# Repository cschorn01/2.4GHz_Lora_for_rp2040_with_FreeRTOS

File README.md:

# Raspberry Pi Pico LoRa Template

<!-- Emoji Cheat Sheet: https://github.com/ikatyang/emoji-cheat-sheet/blob/master/README.md -->

<!--  -->

<!--  -->

## 

The **2.4GHz_Lora_for_rp2040_with_FreeRTOS** is an open source project based on the [Raspberry Pi Pico](https://www.raspberrypi.com/products/raspberry-pi-pico/), [Lora Radio](https://www.semtech.com/products/wireless-rf/lora-connect/sx1280), and [FreeRTOS](https://www.freertos.org/). It's goal is to give hobbyists and developers a strong starting point for their projects involving Lora. This project uses the [PHY layer](https://lora-developers.semtech.com/documentation/tech-papers-and-guides/lora-and-lorawan) of the LoRa radio, with [LoRaWAN](https://lora-developers.semtech.com/documentation/tech-papers-and-guides/lora-and-lorawan) functionality coming.

## 

This project uses a Raspberry Pi Pico's SPI bus to communicate with a 2.4GHz LoRa radio. With FreeRTOS we can create a new task, or individually addressable superloop, that interacts with the [`vSx1280Task`](https://github.com/cschorn01/2.4GHz_Lora_for_rp2040_with_FreeRTOS/blob/44e7e5acd0a1cb4129e875321e36d574b70024c7/src/main.c#L970C6-L970C6) independently. 

In this project there are three tasks, and main():
1. `vSimpleLEDTask` is to show the structure of a task with *setup* above an infinite loop, and the blinking of the onboard pico LED in the infinite loop.
2. `vUsbIOTask` takes typed input from a serial monitor over usb. An unsigned 8 bit pointer array is used as a dynamic ascii character array for a 'string', which is NULL terminated. The address of the pointer array is then sent to `vSx1280Task` to send over LoRa.
3. `vSx1280Task` receives the address of the pointer array from `vUsbIOTask` through a *Task Notification* and reassigns the address to a task local pointer. This is done because there are functions called which delay `vSx1280Task` and would allow `vUsbIOTask` to overwrite the address passed by *Task Notifications*. Once the data is task local `vSx1280Task` will perform a Tx operation, followed by an Rx operation. Both operations are done by using the `sx1280Setup`, `sx1280Tx`, and `sx1280Rx` functions, also in `main.c`.

## 

- :file_folder: pico_projects
  - :file_folder: [Raspberry Pi Pico C SDK](https://github.com/raspberrypi/pico-sdk)
  - :file_folder: [2.4GHz_Lora_for_rp2040_with_FreeRTOS](https://github.com/cschorn01/2.4GHz_Lora_for_rp2040_with_FreeRTOS/) 
    - :file_folder: [Docs](https://github.com/cschorn01/2.4GHz_Lora_for_rp2040_with_FreeRTOS/tree/main/docs)  
    - :file_folder: [FreeRTOS-Kernel](https://github.com/FreeRTOS/FreeRTOS-Kernel)
    - :file_folder: [src](https://github.com/cschorn01/2.4GHz_Lora_for_rp2040_with_FreeRTOS/tree/main/src)  
      - :page_facing_up: [main.c](https://github.com/cschorn01/2.4GHz_Lora_for_rp2040_with_FreeRTOS/blob/main/src/main.c)
    - :file_folder: [include](https://github.com/cschorn01/2.4GHz_Lora_for_rp2040_with_FreeRTOS/tree/main/include)
      - :page_facing_up: [FreeRTOSConfig.h](https://github.com/cschorn01/2.4GHz_Lora_for_rp2040_with_FreeRTOS/tree/main/include/FreeRTOSConfig.h)
    - :page_facing_up: [CMakeLists.txt](https://github.com/cschorn01/2.4GHz_Lora_for_rp2040_with_FreeRTOS/blob/main/CMakeLists.txt)  
    - :page_facing_up: [pico_sdk_import.cmake](https://github.com/cschorn01/2.4GHz_Lora_for_rp2040_with_FreeRTOS/blob/main/pico_sdk_import.cmake)
    - :page_facing_up: [FreeRTOS_Kernel_import.cmake](https://github.com/cschorn01/2.4GHz_Lora_for_rp2040_with_FreeRTOS/blob/main/FreeRTOS_Kernel_import.cmake)

## 

This project is a template to begin a project with a Raspberry Pi Pico, and Lora Modem, for easily adding sensors, or displays.  Then you can create your own long range wireless [Internet of Things](https://en.wikipedia.org/wiki/Internet_of_things) network.  

When adding sensors, create a new task for handling each one. With a new task handling new hardware there must be communication between tasks, which is where [FreeRTOS Task Notifications](https://www.freertos.org/RTOS-task-notifications.html) come in.

In the new task instantiate an 8 bit pointer to store data for sending over SPI:  

>```c
> uint8_t *dataBuffer = NULL;
> ```  
  
Allocate the appropriate amount of memory, in 8 bit chunks, that is needed to send your data:  
  
> ```c
> dataBuffer = ( uint8_t * ) malloc( 255 * sizeof( uint8_t ) );
> ```  

Assign your data to the newly allocated data buffer. Here, 255 is used because it's the maximum LoRa packet size on the sx1280:  
  
>```c
>*( dataBuffer + 0 ) = 0x48; // 0x48 is ASCII Hexadecimal 'H' 
>*( dataBuffer + 1 ) = 0x49; // 0x49 is ASCII Hexadecimal 'I'
>```

Use the [`xTaskNotify()`](https://www.freertos.org/xTaskNotify.html) function to send a *Task Notification* from your new task to `vSx1280Task`. This is where a LoRa message will be sent:

> ```c
> xTaskNotify(  
>             xSx1280TaskHandle,                  /* TaskHandle_t xTaskToNotify */  
>             ( uint32_t ) dataBuffer,            /* uint32_t ulValue (int)&buffer[0] */  
>             eSetValueWithoutOverwrite );        /* eNotifyAction eAction */  
>            )
> ```

To use the incoming *Tast Notification*, it must be reassigned to a task local pointer. This template uses a struct containing an 8 bit pointer:

```c
struct sx1280MessageStorageTillUse{
  uint8_t *message;
};
struct sx1280MessageStorageTillUse messageStorageTillUse = { NULL };
```

<!-- Forkers

 -->

## 

-  `arm-none-eabi-gcc: fatal error: cannot read spec file 'nosys.specs': No such file or directory`
  -  Go to `/usr/bin/local/` delete all files beginning in `arm-none-eabi-` then reinstall the arm toolchain.
    - **Linux:** `sudo apt install cmake gcc-arm-none-eabi libnewlib-arm-none-eabi build-essential`
    - **Mac:** `brew install --cask gcc-arm-embedded`
    - **Windows:** [Pico Setup for Windows](https://github.com/raspberrypi/pico-setup-windows)

<div align="center" dir="auto">
  
</div>

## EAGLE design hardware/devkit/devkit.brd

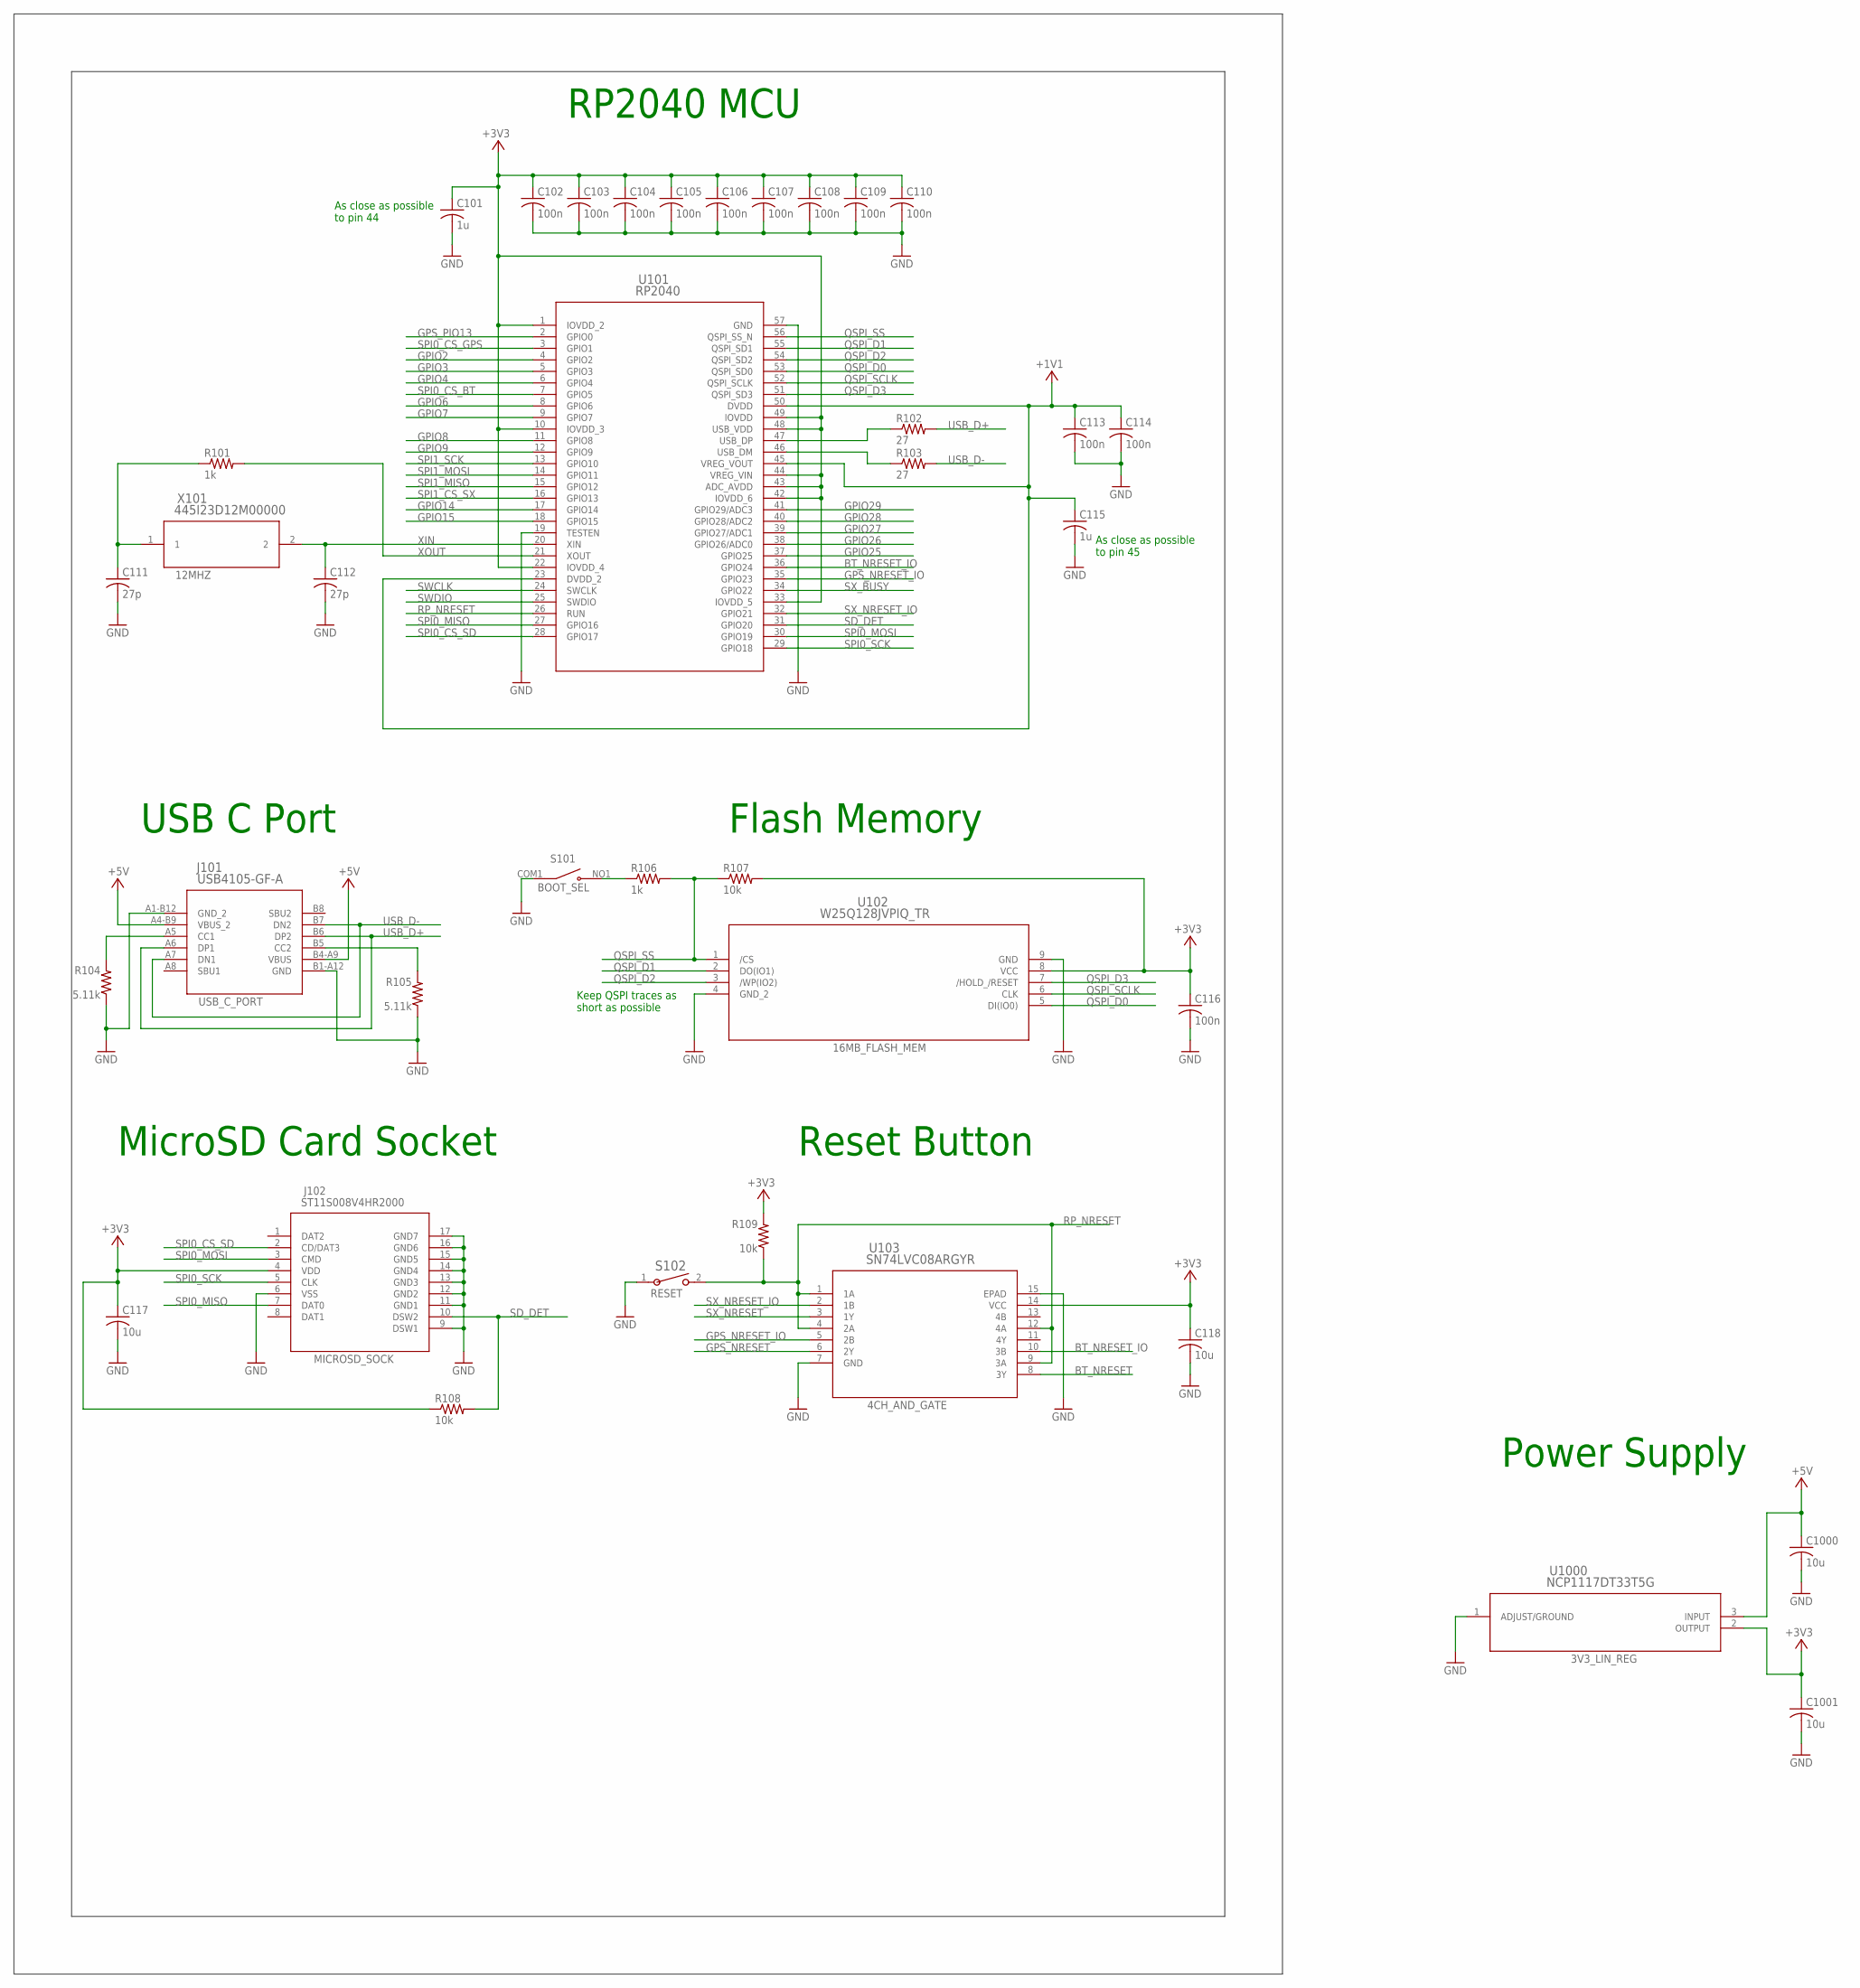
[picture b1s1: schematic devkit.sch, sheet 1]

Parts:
C101, C115: 1u; C0402
C102, C103, C104, C105, C106, C107, C108, C109, C110, C113, C114, C116: 100n; C0402
C111, C112: 27p; C0402
C117, C118, C1000, C1001: 10u; C0402
J101: USB4105-GF-A; USB4105_GCT
J102: ST11S008V4HR2000; ST11S008V4HR2000_JAE
R101, R106: 1k; R0402
R102, R103: 27; R0402
R104, R105: 5.11k; R0402
R107, R108, R109: 10k; R0402
S101: SDA01H1SBD; SW_SDA01H1SBD
S102: PTS820J25MSMTRLFS; SW2_PTS820J25MSMTRLFS_CNK
U101: RP2040; IC57_RP2040
U102: W25Q128JVPIQ_TR; WSON-8_6X5_WIN
U103: SN74LVC08ARGYR; RGY14_2P05X2P05
U1000: NCP1117DT33T5G; DPAK-3_ONS
X101: 445I23D12M00000; 445I23D12M00000_CTS

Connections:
+3V3: C101.1, C102.1, C103.1, C104.1, C105.1, C106.1, C107.1, C108.1, C109.1, C110.1, C116.1, C117.1, C118.1, C1001.1, J102.4 (VDD), R107.2, R108.1, R109.2, U101.1 (IOVDD_2), U101.10 (IOVDD_3), U101.22 (IOVDD_4), U101.33 (IOVDD_5), U101.42 (IOVDD_6), U101.43 (ADC_AVDD), U101.44 (VREG_VIN), U101.48 (USB_VDD), U101.49 (IOVDD), U102.8 (VCC), U103.14 (VCC), U1000.2 (OUTPUT); also elsewhere on the board
+5V: C1000.1, J101.A4-B9 (VBUS_2), J101.B4-A9 (VBUS), U1000.3 (INPUT)
BT_NRESET: U103.8 (3Y)
BT_NRESET_IO: U101.36 (GPIO24), U103.10 (3B)
GND: C101.2, C102.2, C103.2, C104.2, C105.2, C106.2, C107.2, C108.2, C109.2, C110.2, C111.2, C112.2, C113.2, C114.2, C115.2, C116.2, C117.2, C118.2, C1000.2, C1001.2, J101.A1-B12 (GND_2), J101.B1-A12 (GND), J102.6 (VSS), J102.9 (DSW1), J102.11 (GND1), J102.12 (GND2), J102.13 (GND3), J102.14 (GND4), J102.15 (GND5), J102.16 (GND6), J102.17 (GND7), R104.1, R105.1, S101.COM1 (COM), S102.1, U101.19 (TESTEN), U101.57 (GND), U102.4 (GND_2), U102.9 (GND), U103.7 (GND), U103.15 (EPAD), U1000.1 (ADJUST/GROUND); also elsewhere on the board
GPIO2: U101.4 (GPIO2)
GPIO3: U101.5 (GPIO3)
GPIO4: U101.6 (GPIO4)
GPIO6: U101.8 (GPIO6)
GPIO7: U101.9 (GPIO7)
GPIO8: U101.11 (GPIO8)
GPIO9: U101.12 (GPIO9)
GPIO14: U101.17 (GPIO14)
GPIO15: U101.18 (GPIO15)
GPIO25: U101.37 (GPIO25)
GPIO26: U101.38 (GPIO26/ADC0)
GPIO27: U101.39 (GPIO27/ADC1)
GPIO28: U101.40 (GPIO28/ADC2)
GPIO29: U101.41 (GPIO29/ADC3)
GPS_NRESET: U103.6 (2Y); also elsewhere on the board
GPS_NRESET_IO: U101.35 (GPIO23), U103.5 (2B)
GPS_PIO13: U101.2 (GPIO0); also elsewhere on the board
unnamed: R106.1, S101.NO1 (NO)
unnamed: R102.1, U101.47 (USB_DP)
unnamed: R103.1, U101.46 (USB_DM)
unnamed: C111.1, R101.1, X101.1
unnamed: J101.B5 (CC2), R105.2
unnamed: J101.A5 (CC1), R104.2
QSPI_D0: U101.53 (QSPI_SD0), U102.5 (DI(IO0))
QSPI_D1: U101.55 (QSPI_SD1), U102.2 (DO(IO1))
QSPI_D2: U101.54 (QSPI_SD2), U102.3 (/WP(IO2))
QSPI_D3: U101.51 (QSPI_SD3), U102.7 (/HOLD_/RESET)
QSPI_SCLK: U101.52 (QSPI_SCLK), U102.6 (CLK)
QSPI_SS: R106.2, R107.1, U101.56 (QSPI_SS_N), U102.1 (/CS)
RP_NRESET: R109.1, S102.2, U101.26 (RUN), U103.1 (1A), U103.4 (2A), U103.9 (3A), U103.12 (4A)
SD_DET: J102.10 (DSW2), R108.2, U101.31 (GPIO20)
SPI0_CS_BT: U101.7 (GPIO5)
SPI0_CS_GPS: U101.3 (GPIO1); also elsewhere on the board
SPI0_CS_SD: J102.2 (CD/DAT3), U101.28 (GPIO17)
SPI0_MISO: J102.7 (DAT0), U101.27 (GPIO16); also elsewhere on the board
SPI0_MOSI: J102.3 (CMD), U101.30 (GPIO19); also elsewhere on the board
SPI0_SCK: J102.5 (CLK), U101.29 (GPIO18); also elsewhere on the board
SPI1_CS_SX: U101.16 (GPIO13); also elsewhere on the board
SPI1_MISO: U101.15 (GPIO12); also elsewhere on the board
SPI1_MOSI: U101.14 (GPIO11); also elsewhere on the board
SPI1_SCK: U101.13 (GPIO10); also elsewhere on the board
SWCLK: U101.24 (SWCLK)
SWDIO: U101.25 (SWDIO)
SX_BUSY: U101.34 (GPIO22); also elsewhere on the board
SX_NRESET: U103.3 (1Y); also elsewhere on the board
SX_NRESET_IO: U101.32 (GPIO21), U103.2 (1B)
USB_D+: J101.A6 (DP1), J101.B6 (DP2), R102.2
USB_D-: J101.A7 (DN1), J101.B7 (DN2), R103.2
VCC: C113.1, C114.1, C115.1, U101.23 (DVDD_2), U101.45 (VREG_VOUT), U101.50 (DVDD)
XIN: C112.1, U101.20 (XIN), X101.2
XOUT: R101.2, U101.21 (XOUT)

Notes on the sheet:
As close as possible to pin 45
Keep QSPI traces as short as possible
As close as possible to pin 44
RP2040 MCU
Reset Button
Power Supply
USB C Port
Flash Memory
MicroSD Card Socket

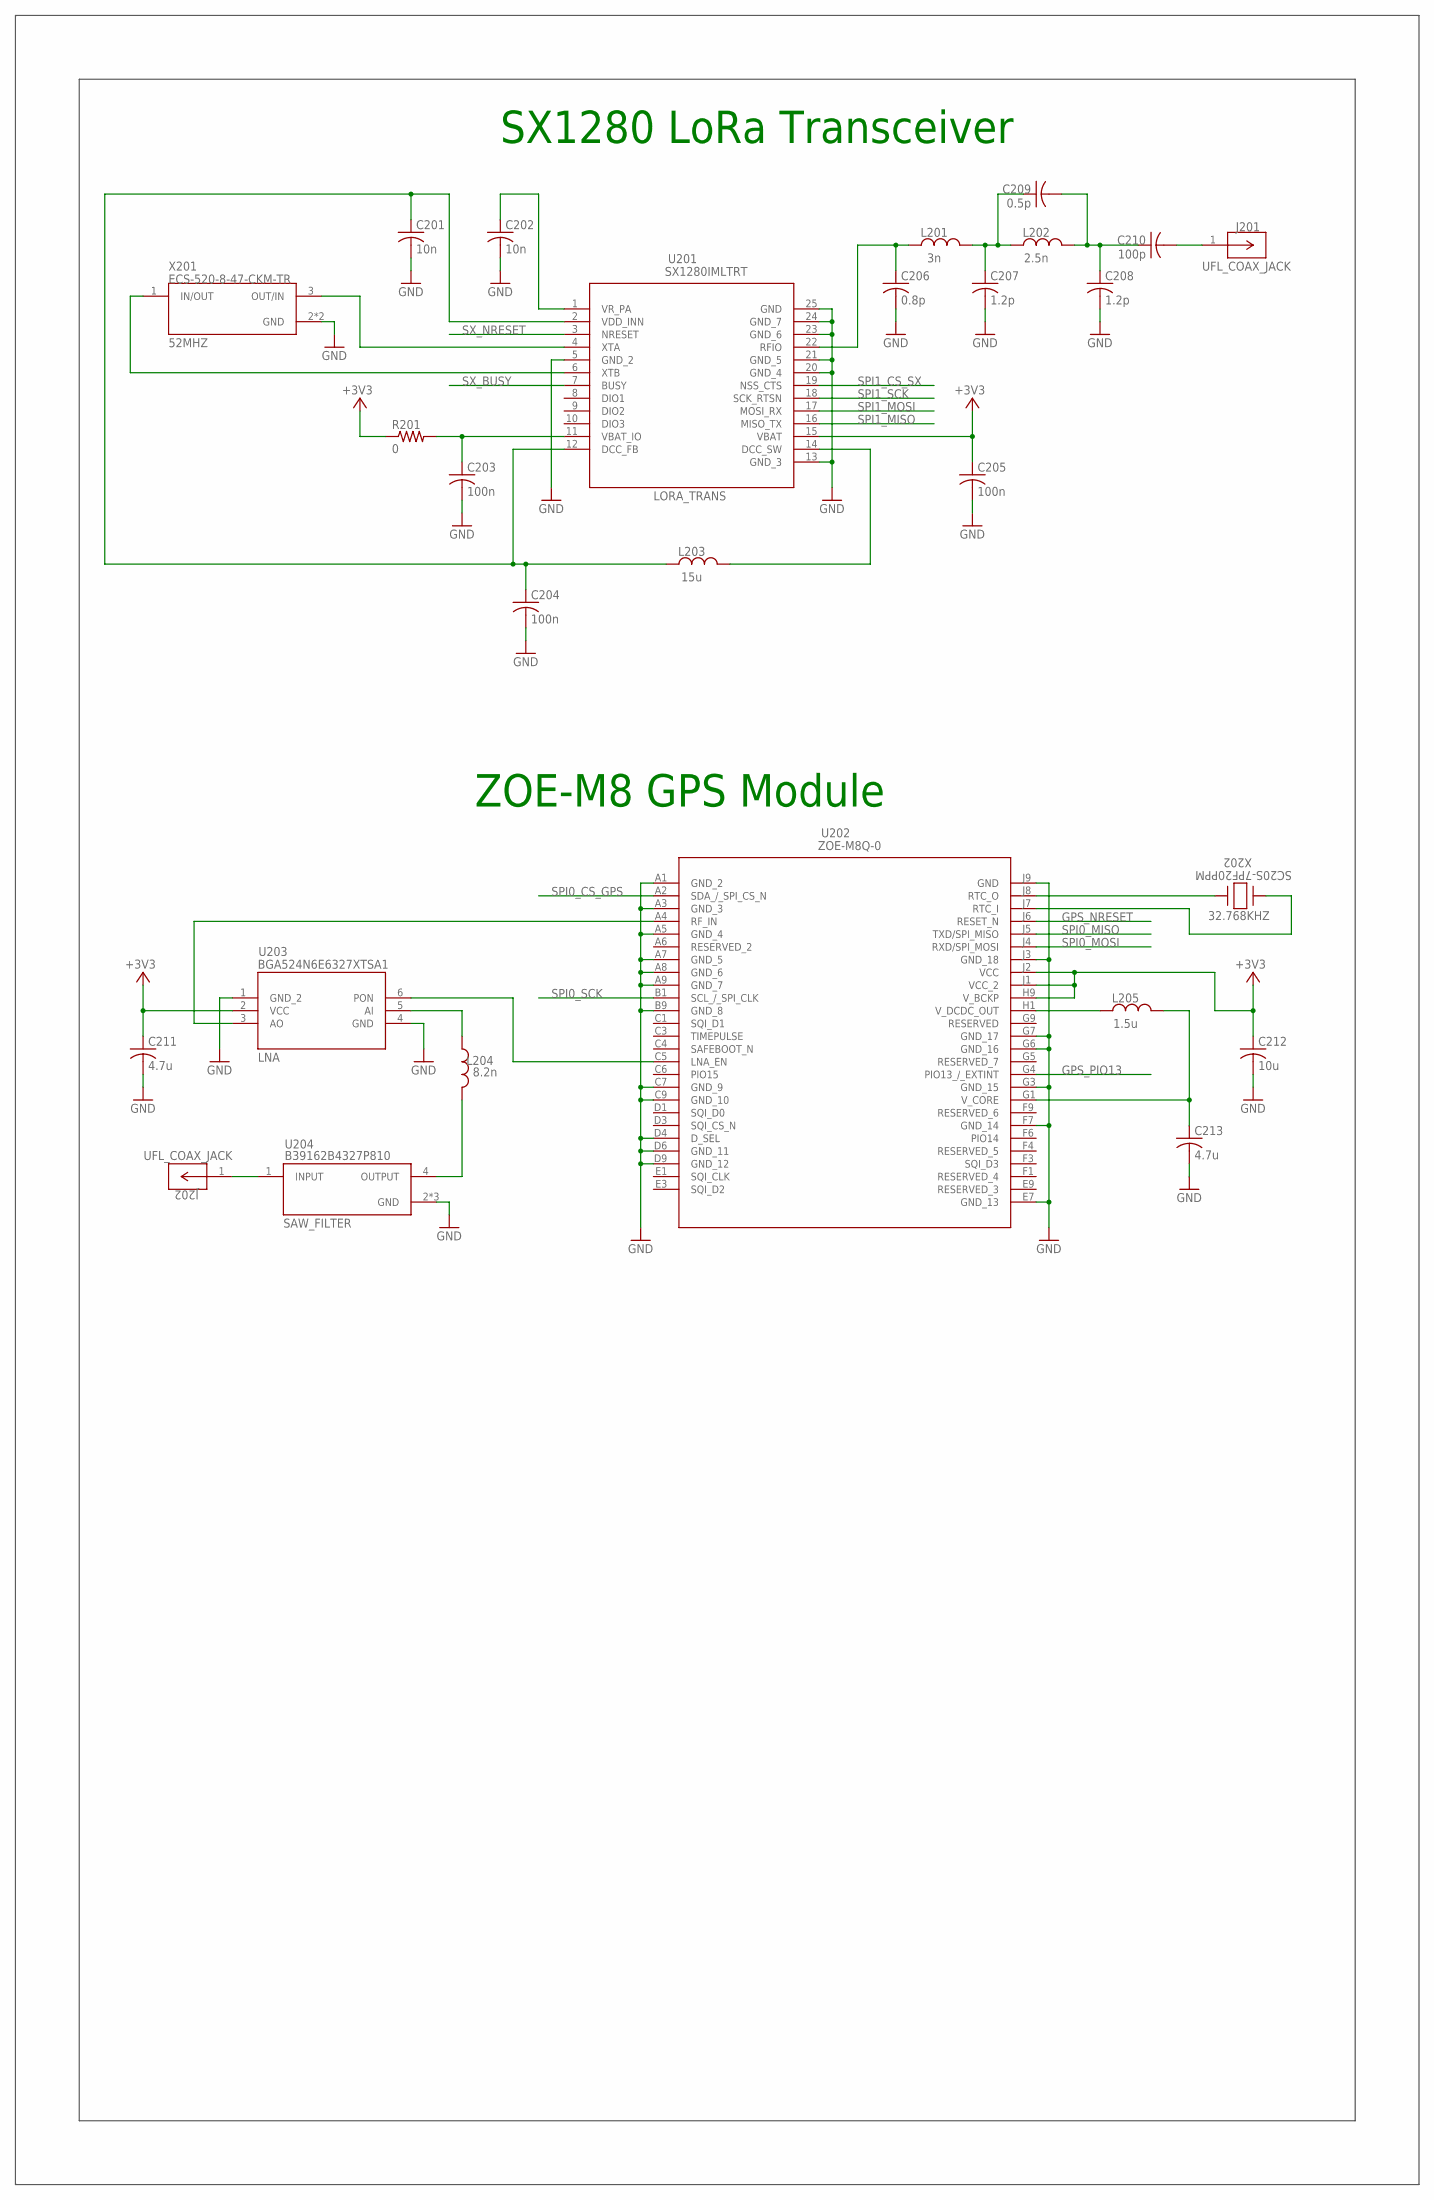
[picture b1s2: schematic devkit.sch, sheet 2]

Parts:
C201, C202: 10n; C0402
C203, C204, C205: 100n; C0402
C206: 0.8p; C0402
C207, C208: 1.2p; C0402
C209: 0.5p; C0402
C210: 100p; C0402
C211, C213: 4.7u; C0402
C212: 10u; C0402
J201, J202: CONUFL001-SMD-T; CONN_CONUFL001-SMD-T_LNX
L201: 3n; INDC1006X60N
L202: 2.5n; INDC1006X60N
L203: 15u; INDC2009X120
L204: 8.2n; INDC1006X60N
L205: 1.5u; INDC2009X120
R201: 0; R0402
U201: SX1280IMLTRT; QFN24_4X4_SEM
U202: ZOE-M8Q-0; BGA_E-M8Q-0_UBL
U203: BGA524N6E6327XTSA1; PG-TSNP-6-2_INF
U204: B39162B4327P810; FIL_B39162B4327P810
X201: ECS-520-8-47-CKM-TR; XTAL_ECS-520-8-47-CKM-TR
X202: SC20S-7PF20PPM; XTAL_SC-20S_EPS

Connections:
+3V3: C205.1, C211.1, C212.1, R201.1, U201.15 (VBAT), U202.H9 (V_BCKP), U202.J1 (VCC_2), U202.J2 (VCC), U203.2 (VCC); also elsewhere on the board
GND: C201.2, C202.2, C203.2, C204.2, C205.2, C206.2, C207.2, C208.2, C211.2, C212.2, C213.2, U201.5 (GND_2), U201.13 (GND_3), U201.20 (GND_4), U201.21 (GND_5), U201.23 (GND_6), U201.24 (GND_7), U201.25 (GND), U202.A1 (GND_2), U202.A3 (GND_3), U202.A5 (GND_4), U202.A7 (GND_5), U202.A8 (GND_6), U202.A9 (GND_7), U202.B9 (GND_8), U202.C7 (GND_9), U202.C9 (GND_10), U202.D4 (D_SEL), U202.D6 (GND_11), U202.D9 (GND_12), U202.E7 (GND_13), U202.F7 (GND_14), U202.G3 (GND_15), U202.G6 (GND_16), U202.G7 (GND_17), U202.J3 (GND_18), U202.J9 (GND), U203.1 (GND_2), U203.4 (GND), U204.2 (GND), U204.3 (GND), U204.5 (GND), X201.2 (GND), X201.4 (GND); also elsewhere on the board
GPS_NRESET: U202.J6 (RESET_N); also elsewhere on the board
GPS_PIO13: U202.G4 (PIO13_/_EXTINT); also elsewhere on the board
unnamed: C203.1, R201.2, U201.11 (VBAT_IO)
unnamed: L203.2, U201.14 (DCC_SW)
unnamed: C210.2, J201.1
unnamed: C201.1, C204.1, L203.1, U201.2 (VDD_INN), U201.12 (DCC_FB)
unnamed: C202.1, U201.1 (VR_PA)
unnamed: U201.6 (XTB), X201.1 (IN/OUT)
unnamed: U201.4 (XTA), X201.3 (OUT/IN)
unnamed: C208.1, C209.2, C210.1, L202.2
unnamed: C207.1, C209.1, L201.2, L202.1
unnamed: J202.1, U204.1 (INPUT)
unnamed: C206.1, L201.1, U201.22 (RFIO)
unnamed: L204.1, U203.5 (AI)
unnamed: L204.2, U204.4 (OUTPUT)
unnamed: U202.J8 (RTC_O), X202.2
unnamed: U202.J7 (RTC_I), X202.1
unnamed: L205.1, U202.H1 (V_DCDC_OUT)
unnamed: U202.A4 (RF_IN), U203.3 (AO)
unnamed: U202.C5 (LNA_EN), U203.6 (PON)
SPI0_CS_GPS: U202.A2 (SDA_/_SPI_CS_N); also elsewhere on the board
SPI0_MISO: U202.J5 (TXD/SPI_MISO); also elsewhere on the board
SPI0_MOSI: U202.J4 (RXD/SPI_MOSI); also elsewhere on the board
SPI0_SCK: U202.B1 (SCL_/_SPI_CLK); also elsewhere on the board
SPI1_CS_SX: U201.19 (NSS_CTS); also elsewhere on the board
SPI1_MISO: U201.16 (MISO_TX); also elsewhere on the board
SPI1_MOSI: U201.17 (MOSI_RX); also elsewhere on the board
SPI1_SCK: U201.18 (SCK_RTSN); also elsewhere on the board
SX_BUSY: U201.7 (BUSY); also elsewhere on the board
SX_NRESET: U201.3 (NRESET); also elsewhere on the board
U1: C213.1, L205.2, U202.G1 (V_CORE)

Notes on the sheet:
SX1280 LoRa Transceiver
ZOE-M8 GPS Module

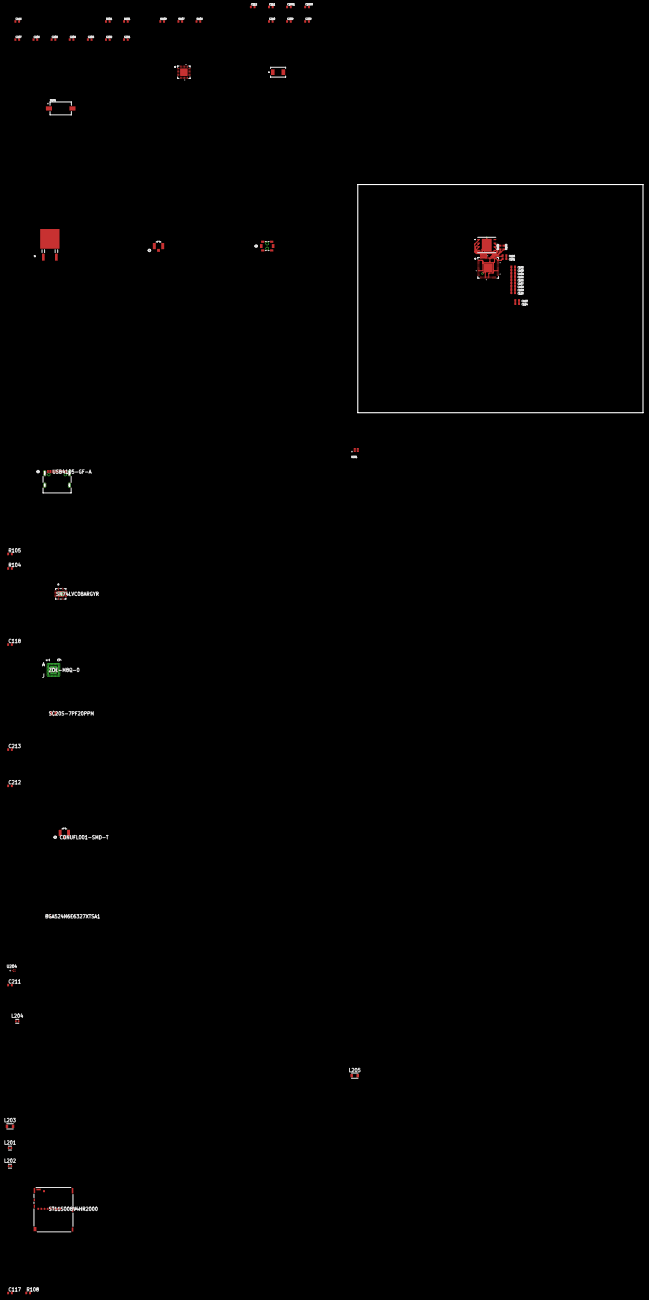
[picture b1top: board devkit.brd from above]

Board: 2 copper layers, 65 parts (0 on the bottom side), 57 nets.

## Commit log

2022-08-11 update docs
2023-07-27 Add files via upload
    Changed the malloc and free to vPortFree and pvPortMalloc, due to changing to heap4. Possibly changing to heap5 due to rp2040 having 4 64kb memory banks
2023-07-30 Add files via upload
    Changed realloc in vUsbIOTask

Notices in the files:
README.md:
MIT License
parts and their libraries:
COPYRIGHT: Copyright (C) 2022 Ultra Librarian. All rights reserved.
